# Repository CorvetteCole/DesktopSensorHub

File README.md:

# DesktopSensorHub
A board designed to connect to a desktop computer via USB, and add sensors such as ambient light, color, proximity, gestures, and more via standard Linux IIO

## Preview (from OSHPark)

## Software references
- Article about the below: https://hackaday.com/2022/10/31/need-an-usb-i2c-adapter-use-your-pico/
- Repo for RP2040 i2c interface: https://github.com/Nicolai-Electronics/rp2040-i2c-interface
- Linux module compilation/setup: https://petermolnar.net/article/linux-i2c-iio-collectd/

## Board references
- Adafruit breakout for Avago APDS9960 proxmity, ALS, color, gesture sensor: https://www.adafruit.com/product/3595
- Adafruit QT2040 board for i2c -> USB: https://www.adafruit.com/product/5056

## Roadmap
- [x] Test prototype once boards arrive
  - Problem encountered, APDS9960 iio i2c driver needs an interrupt, but no interrupt is provided via RP2040 i2c bridge. Need to figure out if we can somehow provide an interrupt over USB or maybe by acting as a GPIO expander as well
- [x] Design PCB, preferrably with USB-C connector on sensor hub
- [ ] Design 3D printed case for sensor so it can mount on top of your PC like a webcam (maybe?)
- [x] Test v1 PCB
  - With much pain, eventually 1 working board as a result, lessons learned
- [ ] Optimize, reduce footprint
  - Remove button, switch to small header, move RP2040 & flash closer to USB port
  - Remove capacitors from USB data lines (not needed)
  - Add test points for APDS9960
  - Move APDS9960 to front of board for ease of assembly
  - Switch to crystal with smaller footprint (less tall)
  - Change test points to plates through holes(?)
  - Break out some extra GPIO because why not
- [ ] Test v2 PCB
- [ ] Release, make repo public (probably no one will care)
- [ ] Write userspace daemon to handle gestures, color temperature calculation and display color adjustment. Would handle display brightness adjustment too, but I think that would be better served by [wluma](https://github.com/maximbaz/wluma)
- [ ] Figure out if wake on proximity sensor is possible

## Related projects
- ColorhugALS: https://blogs.gnome.org/hughsie/2015/05/27/colorhugals-and-sensor-hid/ by https://hughsie.com/. Maybe send him an email once you have something interesting?

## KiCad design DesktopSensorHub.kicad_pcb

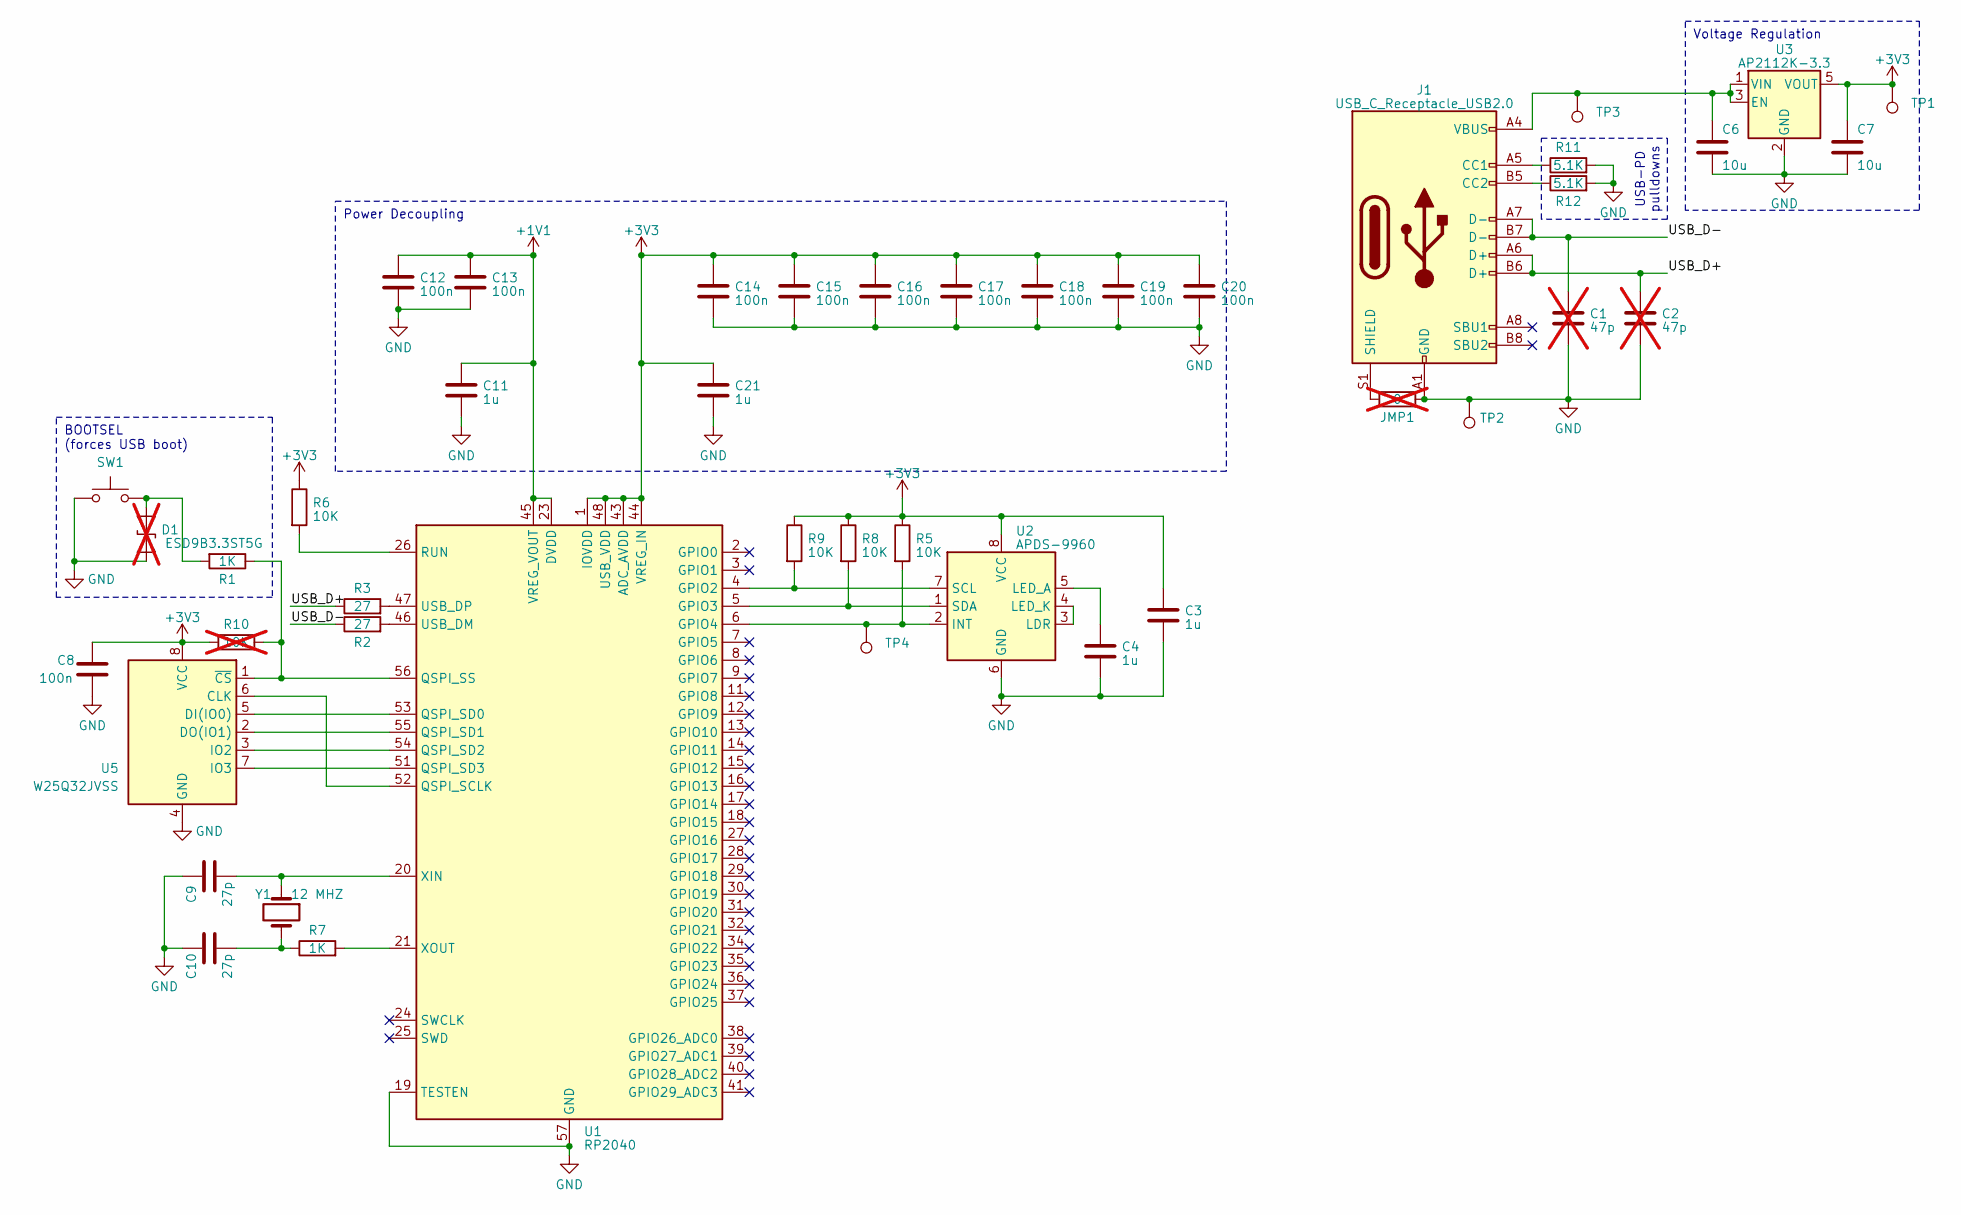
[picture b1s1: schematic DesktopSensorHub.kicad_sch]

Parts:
C1, C2: 47p; C_0402_1005Metric; not fitted
C3, C4, C11, C21: 1u; C_0402_1005Metric
C6, C7: 10u; C_0805_2012Metric
C8, C12, C13, C14, C15, C16, C17, C18, C19, C20: 100n; C_0402_1005Metric
C9, C10: 27p; C_0402_1005Metric
D1: ESD9B3.3ST5G; D_SOD-923; not fitted
J1: USB_C_Receptacle_USB2.0; USB_C_Receptacle_GCT_USB4105-xx-A_16P_TopMnt_Horizontal; MPN USB4105-GF-A
JMP1: 0; SolderJumper-2_P1.3mm_Open_TrianglePad1.0x1.5mm; not fitted
R1: 1K; R_0402_1005Metric; Tolerance 1%
R2, R3: 27; R_0402_1005Metric; Tolerance 1%
R5, R6, R8, R9: 10K; R_0402_1005Metric
R7: 1K; R_0402_1005Metric
R10: 10K; R_0402_1005Metric; not fitted
R11, R12: 5.1K; R_0402_1005Metric
SW1: TS02-66-50-BK-160-LCR-D; SW_PUSH_6mm_H5mm
TP1, TP2, TP3, TP4: TestPoint; TestPoint_Pad_D1.5mm
U1: RP2040; RP2040-QFN-56
U2: APDS-9960; Avago_APDS-9960
U3: AP2112K-3.3; SOT-23-5
U5: W25Q32JVSS; SOIC-8_5.275x5.275mm_P1.27mm
Y1: 12 MHZ; Crystal_SMD_HC49-SD; MPN ABLS-12.000MHZ-B4-T

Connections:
+1V1: C11.1, C12.1, C13.1, U1.23 (DVDD), U1.45 (VREG_VOUT), U1.50 (DVDD)
+3V3: C3.1, C7.1, C8.1, C14.1, C15.1, C16.1, C17.1, C18.1, C19.1, C20.1, C21.1, R5.1, R6.1, R8.1, R9.1, R10.1, TP1.1, U1.1 (IOVDD), U1.10 (IOVDD), U1.22 (IOVDD), U1.33 (IOVDD), U1.42 (IOVDD), U1.43 (ADC_AVDD), U1.44 (VREG_IN), U1.48 (USB_VDD), U1.49 (IOVDD), U2.8 (VCC), U3.5 (VOUT), U5.8 (VCC)
/USB_D+: C2.1, J1.A6 (D+), J1.B6 (D+), R3.1
/USB_D-: C1.1, J1.A7 (D-), J1.B7 (D-), R2.1
GND: C1.2, C2.2, C3.2, C4.2, C6.2, C7.2, C8.2, C9.1, C10.1, C11.2, C12.2, C13.2, C14.2, C15.2, C16.2, C17.2, C18.2, C19.2, C20.2, C21.2, D1.2 (A2), J1.A1 (GND), J1.A12 (GND), J1.B1 (GND), J1.B12 (GND), JMP1.2, R11.2, R12.2, SW1.1, TP2.1, U1.19 (TESTEN), U1.57 (GND), U2.6 (GND), U3.2 (GND), U5.4 (GND)
unnamed: C10.2, R7.1, Y1.2
unnamed: D1.1 (A1), R1.2, SW1.2
unnamed: J1.A5 (CC1), R11.1
unnamed: J1.B5 (CC2), R12.1
unnamed: J1.S1 (SHIELD), JMP1.1
unnamed: R9.2, U1.4 (GPIO2), U2.7 (SCL)
unnamed: R8.2, U1.5 (GPIO3), U2.1 (SDA)
unnamed: R5.2, TP4.1, U1.6 (GPIO4), U2.2 (INT)
unnamed: U1.52 (QSPI_SCLK), U5.6 (CLK)
unnamed: U1.53 (QSPI_SD0), U5.5 (DI(IO0))
unnamed: U1.55 (QSPI_SD1), U5.2 (DO(IO1))
unnamed: U1.54 (QSPI_SD2), U5.3 (IO2)
unnamed: U1.51 (QSPI_SD3), U5.7 (IO3)
unnamed: R1.1, R10.2, U1.56 (QSPI_SS), U5.1 (~CS)
unnamed: R6.2, U1.26 (RUN)
unnamed: R2.2, U1.46 (USB_DM)
unnamed: R3.2, U1.47 (USB_DP)
unnamed: C9.2, U1.20 (XIN), Y1.1
unnamed: R7.2, U1.21 (XOUT)
unnamed: U2.3 (LDR), U2.4 (LED_K)
unnamed: C4.1, U2.5 (LED_A)
unnamed: C6.1, J1.A4 (VBUS), J1.A9 (VBUS), J1.B4 (VBUS), J1.B9 (VBUS), TP3.1, U3.1 (VIN), U3.3 (EN)

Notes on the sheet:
BOOTSEL (forces USB boot)
Voltage Regulation
USB-PD pulldowns
Power Decoupling

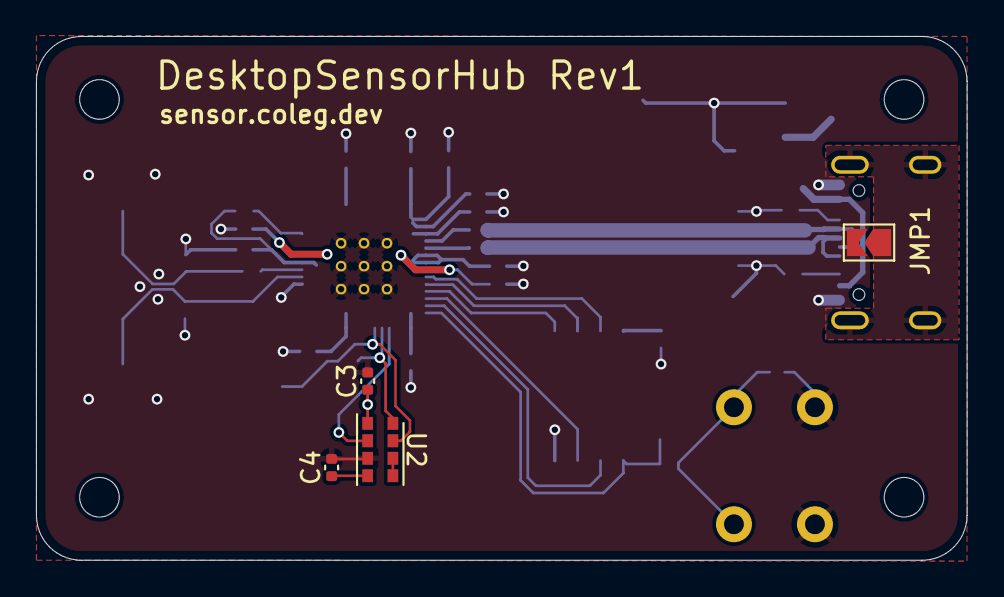
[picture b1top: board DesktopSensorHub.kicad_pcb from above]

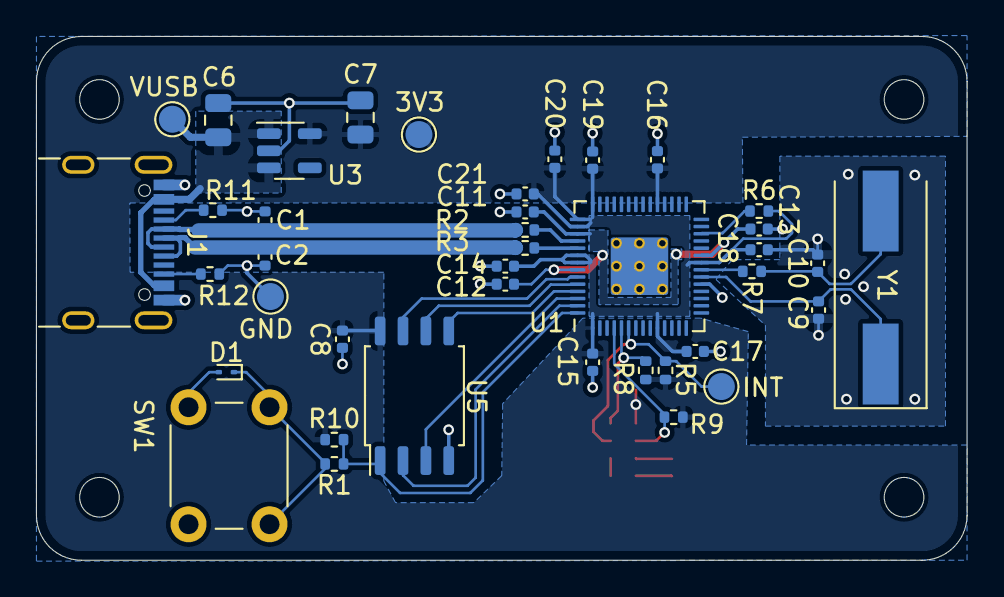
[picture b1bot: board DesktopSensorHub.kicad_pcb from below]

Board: 2 copper layers, 51.7 x 29.1 mm, 44 parts (40 on the bottom side), 27 nets.

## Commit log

2023-01-12 add some web resources for RP2040
2023-01-12 add roadmap
2023-03-21 update status
2023-03-21 fix formatting
2023-03-22 unfinished schematic, but close
2023-03-22 rev1 schematic finished
2023-04-04 mark additional components as do not populate
2023-04-04 remove 100uF capacitor since LED not exposed to be driven externally anyways
2023-04-04 add missing footprint for 1uF capacitors
2023-04-08 final minor tweaks to BOM
2023-04-11 varius small changes to approach a layout
2023-04-17 finish layout, include design files sent to OSHPark
2023-04-20 add oshpark provided images
2023-04-20 add images to readme
2023-05-02 add learned lessons from v1

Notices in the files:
DesktopSensorHub.kicad_sch:
https://creativecommons.org/licenses/by-sa/4.0
Released under the Creative Commons Attribution Share-Alike 4.0 License
